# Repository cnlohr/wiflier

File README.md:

# wiflier, An ESP8266-based Quadcopter Brain

WARNING: This project is still in its early stages!  It doesn't fly yet!

WARNING: Everything surrounding a control loop in control.c for flight IS SUPER JANKEY AND TOTALLY NOT HOW IT SHOULD BE!

WARNING: When I operated the PWM at 3kHz, I had to modify my current board to add pullups on the I2C and short out the AVR's reset to VBat, otherwise it seemed to reboot randomly during flight.

Do you think quadcopters are neat?  Eh, not really for me... BUT I THINK ESP8266's ARE AWESOME!  So, I slapped an LSM9DS1 IMU, a BMP085 barometer and an AVR co-processor with 4 PWM output drivers to a PCB small enough to fit in a hubsan X4 quadcopter.

Picture of the wiflier brain

Youtube video of the first crack at this:

[!(http://img.youtube.com/vi/3n76iMTHXuE/0.jpg)](http://www.youtube.com/watch?v=3n76iMTHXuE) 

## The Hardware

There is an ESP8266, a 32-bit 80(or 160)MHz processor with 802.11bgn networking at the heart of the system.  This run all the user interface code, and handles all control algorithms.  It is attached to a 2 MByte flash for code and data storage.  It is connected via a software i2c bus to:

* An ATTiny441 with 4 PWM outputs and battery voltage monitoring.
   * 4 6-amp N-channel fets, with diode proection on the AVR's output channels to drive DC motors.
   * Safe-mode, which ramps PWM down after periods of inactivity.
* A LSM9DS1, 9-axis IMU with temperature sensor.  It has a gyro, accelerometer, and magnetometer built in.
* A BMP085, barometer with high precision temperature sensor built in.

## Network connectivity

The wiflier uses an ESP8266, which can act as either a station (mode 1) or a softap (mode 2).  Softap means it broadcasts a SSID that other compuers can connect to.

### Station (Mode 1)

Station mode can be initialized by the ```W1:[ssid]:password``` command.  This will cause the wiflier to connect to the specified network.  It supports WEP, WPA-PSK, and WPA2-PSK.  It will remember this setting when it boots up.  If it fails to connect, it will revert to mode 2.  Currently (maybe?) if it reverts to mode 2, it will stay in mode 2 every subsequent bootup.

If it succeeds in negotiating, it will pull a DHCP lease and print to the serial terminal what that DHCP release is.  All communicat

### Soft AP (Mode 2)

Soft AP mode allows the ESP8266 to create its own wifi network that you can connect to with a wifi-enabled device.  In this mode, one can connect to the new network, and visit the ESP at 192.168.4.1.

This is the default mode.

## Command Interfaces

There are currently two command interfaces to the wiflier.  One is UDP, on port 7777, the other is via HTTP at http://[ip]/d/issue?.

### The UDP interface

For the UDP interface, you can use netcat or 'nc' to communicate with the ESP.  This is partciularly convenient as a command-line tool. You can type

```
nc [ip] 7777 -u
```

To open a terminal to the wiflier.  You can type `T1` and enter.  This should provide a constant stream of telemetry.

When using the UDP interface, you must only have one command per packet.  Packets are the delineation of commands.

### The HTTP interface

If you make an HTTP request to `http://[ip]/d/issue?[command]` where [ip] is the address of the wiflier, and [command] is the command you are issuing, the command will be executed and its return value is sent.  You can check this interface's functionality by going to `http://192.168.4.1/d/issue?T0` and verify it returns a T0 confirmation.  Anything after the question mark will be urldecoded.  Things like amphersands should be URL encoded.

### The websockets interface.

This interface does not yet exist, but I hope to make it a reality.

## Building

This code is separated into two pieces, the ESP firmware and the AVR firmware.

The ESP firmware requires the esp_iot_sdk_v1.1.0, and a copy of the ESP8266 GCC toolchain.  To build the ESP firmware, cd to the espfirmware folder and type 'make'.

The AVR firmware requires avr-libc-1.8.0 and avr-gcc-4.8.1 at a minimum.  To build the AVR firmware, cd to the avr folder, and type 'make'.

## Memory layout:

We use a bit of a modified take on the old memory layout since, while we support OTA upgrades, we do so in a different way than the normal way.

| Address | Size  | Name / Description            |
| ------- |:-----:| ----------------------------- |
| 00000h  | 64k   | 0x00000.bin, IRAM Code        | 
| 10000h  | 180k  | Normally unused, HTTP may be here if signature found.  |
| 3C000h  | 4k    | May be used by web interface  |
| 3D000h  | 4k    | our device configuration      |
| 3E000h  | 8k    | May be used by ESP SDK.       |
| 40000h  | 240k  | 0x40000.bin, Cached code.     |
| 7C000h  | 8k    | May be used by ESP SDK.       |
| 7E000h  | 8k    | May be WiFi configuration     |
| 80000h  | 512k  | Scratchpad (Temp only!)       |
| 100000h | 1M+   | HTTP data, 1M on W25Q16.  HTTP Used here if signature found.       |

## Hardware designs

The wiflier schematics and PCB layout is done in KiCad (2013-07-03).  It should be compatible with newer versions, but is unlikely to be compatible with older versions.  In the hardware/ folder, you'll also find wiflier.lst.  This contains the part identifier, name, digikey part number (if applicable) and cost assuming an order of ~10 boards.

## wiflier UART

The UART on the wiflier is used to send debugging information.  The Wiflier does not currently accept commands via the UART.  I intend to make the UART available to GPS or video input.

## UART flashing the ESP8266.

To UART flash the ESP8266 you will need esptool.py and a serial TTL uart.  USB to serial converters are good. *Do not* use RS-232-level UARTs.  To flash this, you will need to:

1. De-power the device. 
2. Connect GPIO0 to GND.
3. Connect TX, RX and GND (And possibly power) to your UART, reversing TX/RX lines.
4. Apply power to the device.  
5. Then go to the espfirmware folder, and type:

    ```
    ~/esp8266/esptool/esptool.py --port /dev/ttyUSB0 write_flash 0x00000 0x00000.bin 0x40000 0x40000.bin
    ```
    
    or

    ```
    make burn
    ```

6. The esptool should reboot into the running code.

## Net flashing the ESP8266.

Net Flashing the ESP8266 is particularly easy.  Connect to the wiflier, verify you can communicate to it (via HTTP or ping).  Use the 'execute_reflash' tool with the following commands:

```
web/execute_reflash 192.168.4.1 0x00000.bin 0x40000.bin
```

or, from the espfirmware folder...

```
make netburn
```

This will connect to 192.168.4.1, and it will perform the following steps:

1. It will attempt to erase the blocks that need to be written (to 0x00000.bin) using the "FB" command.
  * And await confirmation.
2. It will write the data (0x00000.bin) using the "FW" command.
  * And await confirmation.
3. It will write this first file to 80000h, then it will repeat for the second file, to c0000h.
4. It will then compute the MD5 of the files and execute the "FM" command.
5. Internally, the wiflier will verify the integrety of the written files.
6. At this point, it will disable all interrupts.  Network will go down, etc.
7. It will copy the data from 80000h to 00000h, and then copy c0000h to 40000h.
8. It will then reboot itself and boot into the new code.
9. If a network wasn't found, and it switches to being its own AP... next boot, it should still try to join the old network.

## Flashing the AVR

The AVR is particularly easy to flash.  You'll need:

  * An ISP Programmer, like the TinyISP that operates a 3.3V outputs.
    * Under *NO* condition use a programmer that haves 5V outputs.  This will almost certainly cause severe damage to the wiflier.
  * Associated 6-pin ISP programming connector.
  * AVRDude, or other ISP programming software.
  * A 6-pin male-male connector, SMD preferred.

To flash, follow the following steps:

  1. Connect to a wiflier command interface.
  2. Use the "B0" command to make the ESP8266 release the bus.
    * Failure to do this may damage the AVR or ESP.
  3. Plug the 6-pin male connector into the programming header on the programmer.
  4. Hold the 6-pin connector on the back of the PCB. 
    * Reversing the order will not program, but will not damage the part.
    * You can determine proper order by unplugging power to the quadcopter and flipping the connector around until it powers on.  Powering on indicates proper order.
  5. Initiate programming of the AVR.
	* Failures may indicate the ESP is locking the bus lines.
    * Failures may indicate not all the pins are making contact.
    * Failures may indicate the programming header is reversed.
    * Failures may indicate other problems in the toolchain, i.e. not running programmer as root or having proper credentials.
  6. Remove programmer.
  7. Use the "B1" command to bring the ESP8266 Back online.

## TODO

### Software modifications:

* Try one-shotting the sensors (currently they're in free-run) this will synchronize them to the system clock.
* Try making the system switch over to calling the control loop on interrupt after connection is negotiated, rather than using flags and the idle loop.
* Add WebSockets?
* Add WebGL?
* Separate the control.c into different parts.
* Have some minimal levels of protection for writing to flash, i.e. maybe only allow writing to 0x80000+
* Send some sort of broadcast or discovery packets.
* Figure out why the AVR needs soooo many bytes before it accepts data.

### Hardware modifications:

* Consider making the sensors slaves to the AVR, and having the ESP communicate only to the AVR.
* Consider using the MPL3115A2 instead of the BMP085
* I keep looking at the lack of pullups on the I2C and it makes me nervous when we're running the motor controllers.

## Commands

The heart of the wiflier is the command engine.  This command engine is human-readable, and with the exception of some use cases of the flashing commands is human-readable.

Commands are very simple, they are basically single letters, then parameters, separated by colons.  Responses are usually similar to the command that was sent.  A failure can be indicated by either a lack of response, or an exclaimation point (!) prefixing the response.

As a warning, in some places \r\n is used and in others \n is used.  You should discard \r in all non-binary uses.

### Bn (B1 / B0):  Turn main control loop on/off
Turning the main control loop off will stop all I2C bus communication and resolving what to do in the control loop.  That also means telemetry will stop.

### D
Reboot the system.  This includes the bootloader.  If GPIO0 is held low, the serial bootloader will be initiated.

### Tn (T1 / T0):  Turn streaming of calibrated, filtered telemetry data on/off
This will either continously stream, or turn off streaming of the calibrated telemetry data from the sensors.  Calibration is done using the Rn and Z commands.  Data is tab deliniated.

The streaming format is: ```TD: [frame #]  [GyroX]  [GyroY]  [GyroZ]  [AccX]  [AccY]  [AccZ]  [MagX]  [MagY]  [MagZ]  [Pressure in Bar]  [Temperature in tenths of degrees C]  [battery voltage in 1/100ths of a volt]\n```

### Un (U1 / U0):  Turn streaming of uncalibrated/raw telemtry data on/off
This will enable/disable streaming of uncalibrated telemetry data, straight from the sensors.   Data is tab deliniated.

The streaming format is: ```UD: [frame #]  [GyroX]  [GyroY]  [GyroZ]  [AccX]  [AccY]  [AccZ]  [MagX]  [MagY]  [MagZ]  [Pressure in Bar]  [Temperature in tenths of degrees C]  [battery voltage in 1/100ths of a volt]\n```

For example:
```
UD   9224      600      199      137     2839     1790     2080       61     2214    -4673    101233    368    499 \r\n
UD   9225     -616     -244      304     3208     1797     1934       40     2229    -4673    101233    368    507 \r\n
UD   9226     -687     -234      318     3374     1815     1893       74     2259    -4683    101233    368    507 \r\n
UD   9227      242      240       43     2960     1795     2051       31     2223    -4691    101233    368    507 \r\n
UD   9228      455      146       46     3122     1708     1964       37     2226    -4664    101237    368    507 \r\n
```

### Z: Set 'zero'
Sending a Z will set the zero all gyros, and accelerometer X and accelerometer Y.  This will only have an effect on the calibrated, filtered telemetry data.

### Rn (R1 / R0): Enable range calibration.
When you want to begin range calibration (for accelerometer Z, and all mag inputs) send R1.  This will begin to look for peak positive and negative values.  When you execute R0, it will take whatever the maximums are and scale all data to that range.

### P: Print calibration and other system data.
When you send a 'P' command, the wiflier will send back all calibration and possibly other system data.  As of the time of writing this the following values are returned:

```
    P6
    #GC\t x \t y \t z (Gyro Zero)
    #AC\t x \t y \t z (Accelerometer Zero)
    #AL\t x \t y \t z (Accelerometer Minimum)
    #AM\t x \t y \t z (Accelerometer Maximum)
    #ML\t x \t y \t z (Magnetometer Minimum)
    #MH\t x \t y \t z (Magnetometer Maximum)
```

### S: Save calibration and other settings.
This writes the current information in the global `settings` value to the flash at address 3D000h.

### Mx: Motor control functions

#### M?: Motor query

Returns if motors are in automatic mode (1/0) and all motor speeds, 0..255 speed.

`M?` will return `M?[automatic]:[M0 speed]:[M1 speed]:[M2 speed]:[M3 speed]\r\n"

#### MA: Motors in automatic mode

Selecting this function will move the move the motors into automatic mode, allowing a control algorithm to take them over.

(Not currently implemented)

#### MM: Motors in manual mode

Disable automatic control of motors, they will now respond to the M(number) commands.  Optionally, can take up to 4 arguments for the new motor set values.

#### M0, M1, M2, M3: Set motor speed.

If you want to control an individual motor speed, you call `Mn:speed` for example `M0:127` would turn motor 0 on to half duty cycle.  This only works if the motors are in manual mode.

### Fx: Flash commands

#### FEn: Flash Erase Sector

Erase a specific flash sector, it will erase the flash starting at address n*4096 to n*4096+4095.  This function works with flash memory below and above the 1MB barrier, however it takes a moment to execute and no interrupts may run while it is executing.

#### FBn: Flash Erase Block

Erase a specific block of flash.  This operates on a whole 64kB block, and takes about as long as it takes FE to erase just one sector.  This function does not work past the 1MB barrier.

#### FW: Flash Write

This function writes flash. It requires two parameters, the first is the starting addres, the second is the size (in bytes).   Writes must be aligned to 4-byte boundaries, sizes must line to 4-byte boundaries.

```
    FW40:8:hello\r\n
```

Will write `hello\r\n\0` to memory address 40 (which will break booting, so don't do this), and it will respond with:

```
    FW40
```

#### FR: Flash Read

This will read back from the flash, starting at the first parameter and with length of the second.

```
    FR40:8\r\n
```

Will read from address 40 8 bytes and if we've executed the terrible terrible example above, respond with:

```
    FR00000040:0008:hello\r\n\0
```

#### FM: Rewrite boot flash

This function takes several parameters, in the style: ```FMa:b:c:d:e:f:g:h``` where 

   1. A = Address to copy from #1
   2. B = Address to copy to #1  (Must be 65kB aligned)
   3. C = Number of bytes to copy #1 (Must be 1k chunks)
   4. D = MD5 of entire 'from #1' range.
   5. E = Address to copy from #2
   6. F = Address to copy to #2  (Must be 65kB aligned)
   7. G = Number of bytes to copy #2 (Must be 1k chunks)
   8. H = MD5 of entire 'from #2' range.

This will verify both MD5's before copying.  Interrupts will continue to execute until the actual flash-over begins.  Once flash-over is complete, the device will automatically reboot.

An example would be:

```
FM524288:0:33792:d6f04e459bc9aefabd9ed80981e6837f:786432:262144:171008:8435d1904110eacb66771320f63736bc
```

It should respond with ```FM``` In the event of a failure, it will also send a ```!FM[code]```.

### Wx: Wireless/Network commands.

#### W1: Connect to wifi network.

If you want to connect to an existing wifi network, you can use the W1 command.  This will find the specified AP, and join.  An example W1 command would be ```W1:ssid:password```.  This will connect to network with name 'ssid', and password 'password'.  If it fails to connect, it will switch back to softap mode.

#### W2: Make softAP network

This will cause the ESP8266 to make its own network. You can connect to it.  Its IP will be 192.168.4.1

#### WI: Get current settings

This will cause the ESP8266 to give you the mode (1 or 2) SSID, and password of the current network status.

For example ```WI``` will return ```WI1:mynetwork:mypassword```.

#### WS: Scan for networks

**WARNING**: If operating in mode 2, this will cause the ESP to go offline momentarily while it scans!

If you issue the ```WS``` command, the ESP8266 will begin a scan. It is unlikely to return any response at all. You can read the returned networks with the ```WR``` command.

It may take several seconds for the WS command to complete.

#### WR: Return wireless networks from last scan.

After you scan for networks, you can probe for responses to those networks with the ```WR``` command.  It returns ```WRn``` where n is the number of networks found.  It will then provide the networks in a tab delinated data format as follows:

```
#SSID MAC RSSI Channel Encryption
```

For example a response to the ```WR``` command could be:

```
WR3
#quiddles       00:23:15:11:22:41       -44     1       open
#reads          08:18:a0:02:4d:cc       -55     1       wpa2
#rguest         0a:14:c1:f3:02:a0       -68     11      open
```

### J: Joystick commands

***SECTION NOT WRITTEN***

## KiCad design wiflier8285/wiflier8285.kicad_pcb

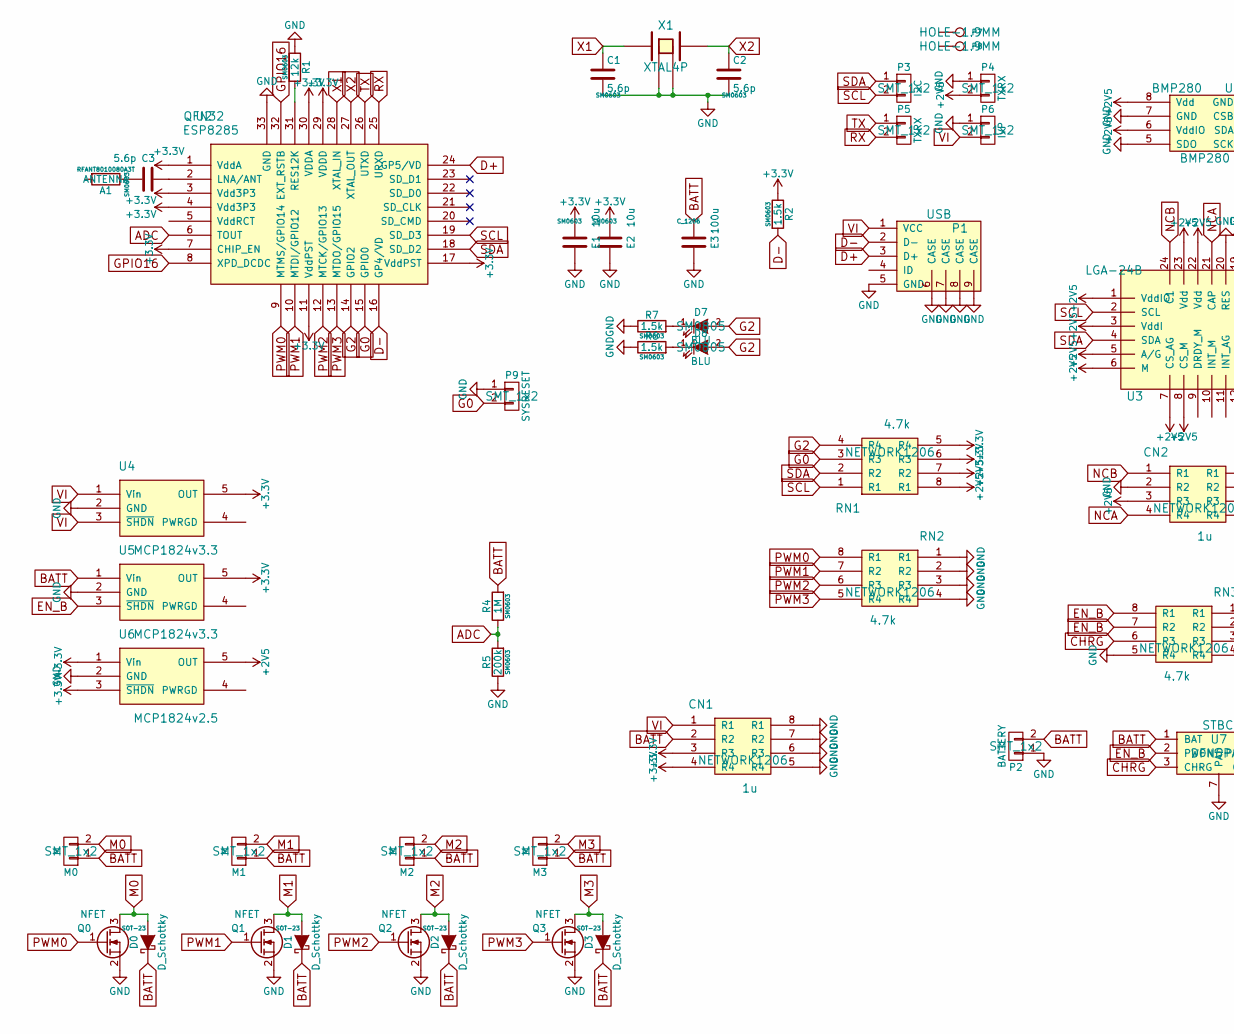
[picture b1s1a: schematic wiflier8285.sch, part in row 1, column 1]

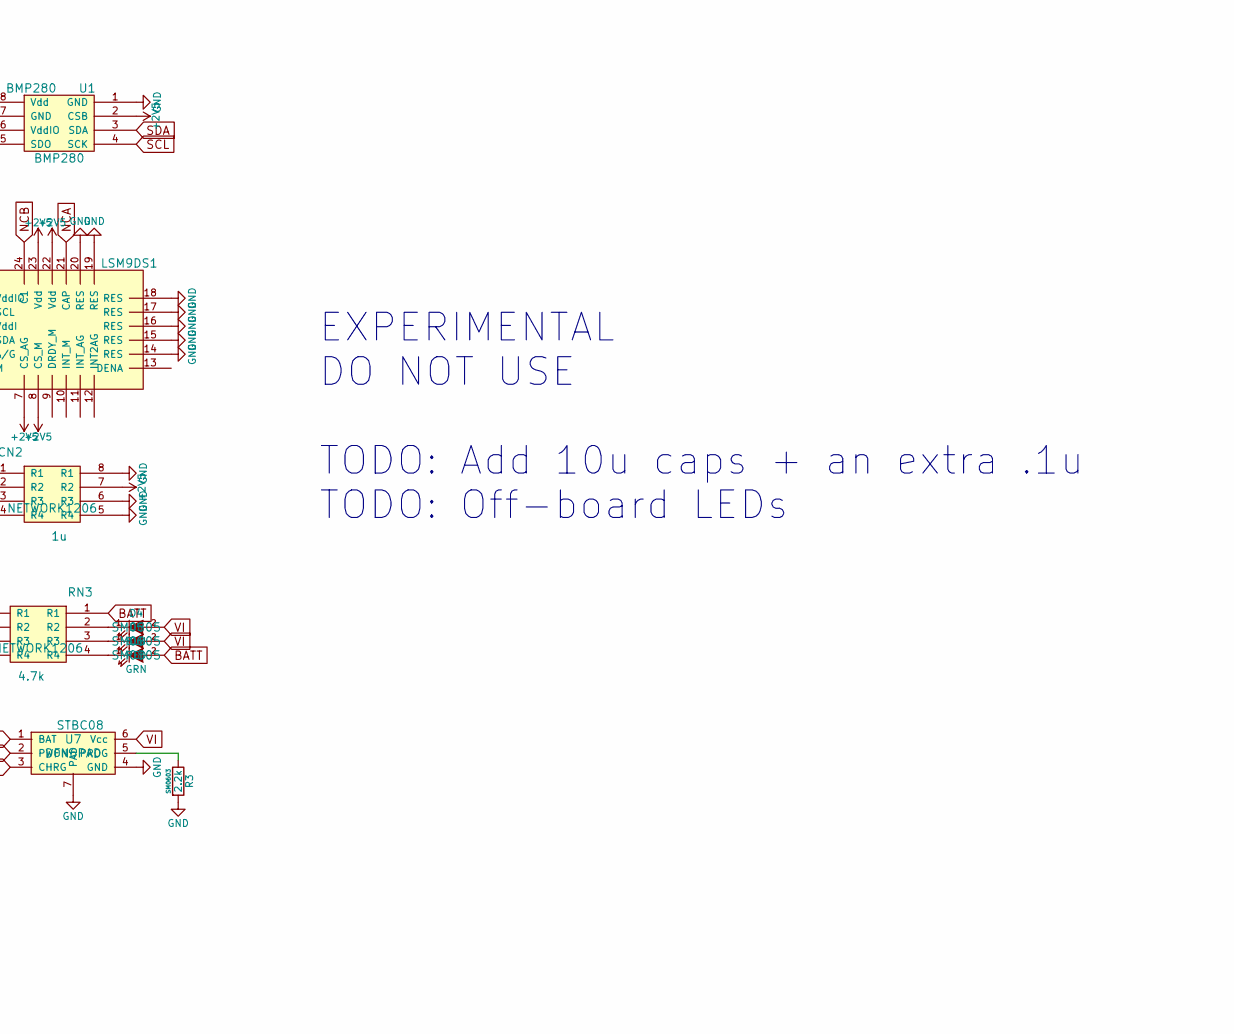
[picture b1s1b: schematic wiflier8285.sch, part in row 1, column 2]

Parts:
A1: ANTENNA; RFANT8010080A3T
C1, C2, C3: 5.6p; SM0603
CN1, CN2: 1u; NETWORK1206
D0, D1, D2, D3: D_Schottky; SMini2-F5-B; Digikey DB2J41100LCT-ND
D4, D7, D8: BLU; SM0805
D5: RED; SM0805
D6: GRN; SM0805
E1, E2: 10u; SM0603
E3: 100u; C_1206
M0, M1, M2, M3: M; SMT_1x2
P1: USB; USBMicroB-10118194-0001LF
P2: BATTERY; SMT_1x2
P3: I2C; SMT_1x2
P4, P5: TXRX; SMT_1x2
P6: IVP; SMT_1x2
P7, P8: M; HOLE-1.9MM
P9: SYSRESET; SMT_1x2
Q0, Q1, Q2, Q3: NFET; SOT-23; Digikey IRLML6244TRPBFCT-ND
R1: 12k; SM0603
R2, R6, R7: 1.5k; SM0603
R3: 2.2k; SM0603
R4: 1M; SM0603
R5: 200k; SM0603
RN1, RN2, RN3: 4.7k; NETWORK1206
U1: BMP280
U2: ESP8285; QFN32
U3: LSM9DS1; LGA-24B
U4, U5: MCP1824v3.3; SOT-23-5
U6: MCP1824v2.5; SOT-23-5
U7: STBC08; DFN6PAD
X1: XTAL4P; XTAL4TINY

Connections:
+2V5: CN2.3 (R3), CN2.7 (R2), P4.2, RN1.7 (R2), RN1.8 (R1), U1.2 (CSB), U1.6 (VddIO), U1.8 (Vdd), U3.1 (VddIO), U3.3 (VddI), U3.5 (A/G), U3.6 (M), U3.7 (CS_AG), U3.8 (CS_M), U3.22 (Vdd), U3.23 (Vdd), U6.5 (OUT)
+3V3: CN1.3 (R3), CN1.4 (R4), E1.2, E2.2, R2.1, RN1.5 (R4), RN1.6 (R3), U2.1 (VddA), U2.3 (Vdd3P3), U2.4 (Vdd3P3), U2.7 (CHIP_EN), U2.11 (VddPST), U2.17 (VddPST), U2.29 (VDDD), U2.30 (VDDA), U4.5 (OUT), U5.5 (OUT), U6.1 (Vin), U6.3 (~SHDN)
ADC: R4.1, R5.2, U2.6 (TOUT)
BATT: CN1.2 (R2), D0.1 (K), D1.1 (K), D2.1 (K), D3.1 (K), D6.2 (A), E3.2, M0.1, M1.1, M2.1, M3.1, P2.2, R4.2, RN3.1 (R1), U5.1 (Vin), U7.1 (BAT)
CHRG: RN3.6 (R3), U7.3 (CHRG)
D+: P1.3 (D+), U2.24 (GP5/VD)
D-: P1.2 (D-), R2.2, U2.16 (GP4/VD)
EN_B: RN3.7 (R2), RN3.8 (R1), U5.3 (~SHDN), U7.2 (PWON)
G0: P9.2, RN1.3 (R3), U2.15 (GPIO0)
G2: D7.2 (A), D8.2 (A), RN1.4 (R4), U2.14 (GPIO2)
GND: C1.2, C2.2, CN1.5 (R4), CN1.6 (R3), CN1.7 (R2), CN1.8 (R1), CN2.2 (R2), CN2.5 (R4), CN2.6 (R3), CN2.8 (R1), E1.1, E2.1, E3.1, P1.5 (GND), P1.6 (CASE), P1.7 (CASE), P1.8 (CASE), P1.9 (CASE), P2.1, P4.1, P6.1, P9.1, Q0.2 (S), Q1.2 (S), Q2.2 (S), Q3.2 (S), R1.1, R3.2, R5.1, R6.1, R7.1, RN2.1 (R1), RN2.2 (R2), RN2.3 (R3), RN2.4 (R4), RN3.5 (R4), U1.1 (GND), U1.5 (SDO), U1.7 (GND), U2.33 (GND), U3.14 (RES), U3.15 (RES), U3.16 (RES), U3.17 (RES), U3.18 (RES), U3.19 (RES), U3.20 (RES), U4.2 (GND), U5.2 (GND), U6.2 (GND), U7.4 (GND), U7.7 (PAD), X1.3 (GND), X1.4 (GND)
GPIO16: U2.8 (XPD_DCDC), U2.32 (EXT_RSTB)
M0: D0.2 (A), M0.2, Q0.3 (D)
M1: D1.2 (A), M1.2, Q1.3 (D)
M2: D2.2 (A), M2.2, Q2.3 (D)
M3: D3.2 (A), M3.2, Q3.3 (D)
NCA: CN2.4 (R4), U3.21 (CAP)
NCB: CN2.1 (R1), U3.24 (C1)
unnamed: A1.1, C3.2
unnamed: C3.1, U2.2 (LNA/ANT)
unnamed: D4.1 (K), RN3.2 (R2)
unnamed: D5.1 (K), RN3.3 (R3)
unnamed: D6.1 (K), RN3.4 (R4)
unnamed: D7.1 (K), R7.2
unnamed: D8.1 (K), R6.2
unnamed: R1.2, U2.31 (RES12K)
unnamed: R3.1, U7.5 (PROG)
PWM0: Q0.1 (G), RN2.8 (R1), U2.9 (MTMS/GPIO14)
PWM1: Q1.1 (G), RN2.7 (R2), U2.10 (MTDI/GPIO12)
PWM2: Q2.1 (G), RN2.6 (R3), U2.12 (MTCK/GPIO13)
PWM3: Q3.1 (G), RN2.5 (R4), U2.13 (MTDO/GPIO15)
RX: P5.2, U2.25 (URXD)
SCL: P3.2, RN1.1 (R1), U1.4 (SCK), U2.19 (SD_D3), U3.2 (SCL)
SDA: P3.1, RN1.2 (R2), U1.3 (SDA), U2.18 (SD_D2), U3.4 (SDA)
TX: P5.1, U2.26 (UTXD)
VI: CN1.1 (R1), D4.2 (A), D5.2 (A), P1.1 (VCC), P6.2, U4.1 (Vin), U4.3 (~SHDN), U7.6 (Vcc)
X1: C1.1, U2.28 (XTAL_IN), X1.1
X2: C2.1, U2.27 (XTAL_OUT), X1.2

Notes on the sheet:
EXPERIMENTAL DO NOT USE TODO: Add 10u caps + an extra .1u TODO: Off-board LEDs

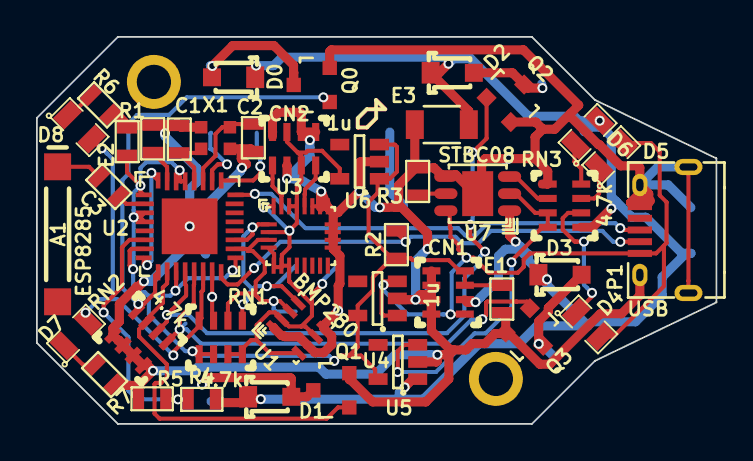
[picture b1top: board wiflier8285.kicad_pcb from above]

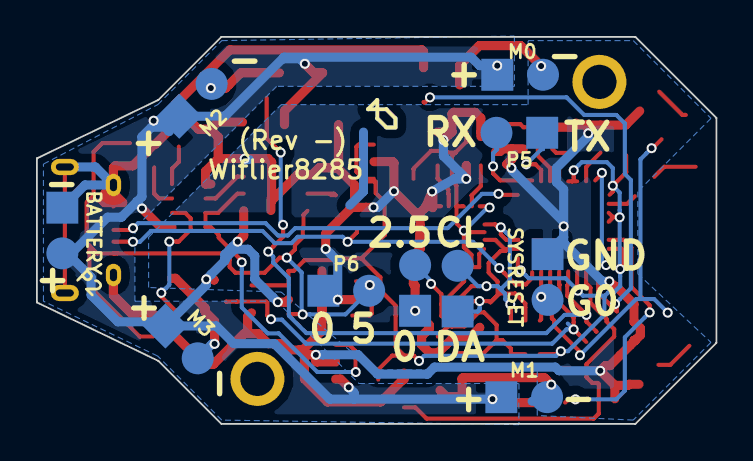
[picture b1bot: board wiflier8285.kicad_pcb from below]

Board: 2 copper layers, 37.8 x 21.5 mm, 53 parts (10 on the bottom side), 38 nets.

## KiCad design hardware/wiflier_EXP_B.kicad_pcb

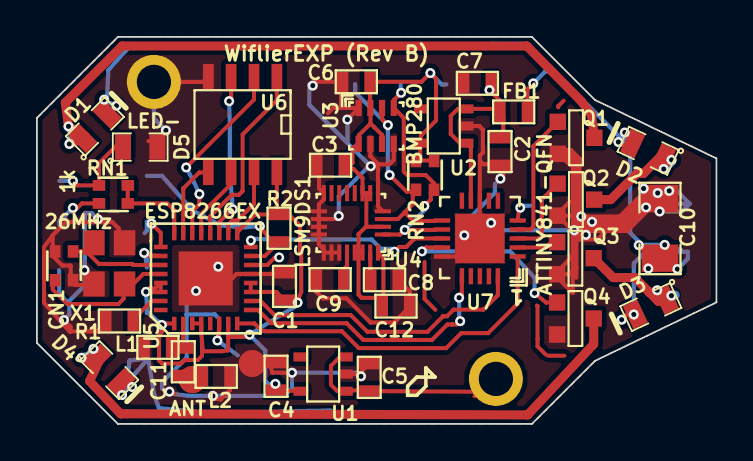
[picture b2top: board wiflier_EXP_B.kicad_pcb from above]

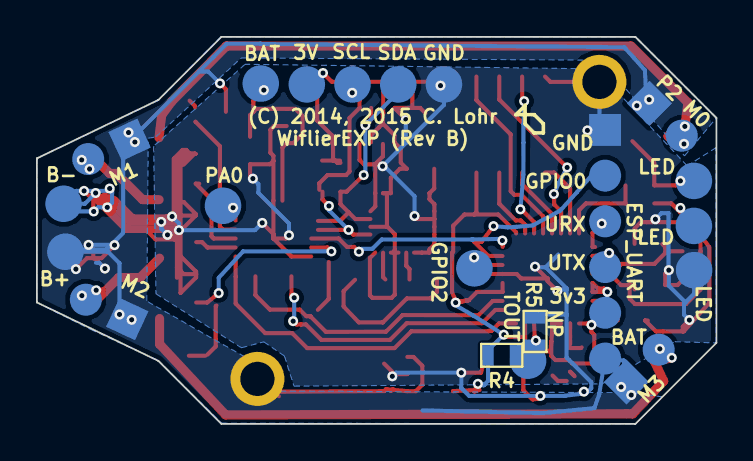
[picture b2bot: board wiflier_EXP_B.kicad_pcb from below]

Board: 2 copper layers, 37.8 x 21.5 mm, 61 parts (20 on the bottom side), 41 nets.

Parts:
C1, C2, C3, C5: 10uF; SM0603
C4: 1uF; SM0603
C6, C8, C12: .1u; SM0603
C7: .1uF; SM0603
C9: 10nF; SM0603
C10: 100uF; SM1206
C11: 5.6pF; SM0603
CN1: 10p; NETWORK0606
D1, D2, D3, D4: 20V_500mA; SM0805
D5: LED-; SM0805
FB1: -; SM0603
L1, L2: NP; SM0603
P1: GPIO2; .1SMTPIN
P2: M0; SMT_1x2
P3: M1; SMT_1x2
P4: M2; SMT_1x2
P5: M3; SMT_1x2
P6, P19: ANT; .1SMTPIN
P7, P8: HOLE-1.9MM
P9: SDA; .1SMTPIN
P10: SCL; .1SMTPIN
P11: 3V; .1SMTPIN
P12: GND; .1SMTPIN
P13, P14, P15: LED; .1SMTPIN
P16: BAT; .1SMTPIN
P17: TOUT; .1SMTPIN
P18: PA0; .1SMTPIN
P21: B+; .1SMTPIN
P24: B-; .1SMTPIN
P32: ESP_UART; SMT_1x6
Q1, Q2, Q3, Q4: 7A_20V; SOT23GDS
R1, R2, R4: 12k; SM0603
R5: NP; SM0603
RN1, RN2: 1k; NETWORK0606
U1: MCP1824/3.3; SOT23-5
U2: MCP1824/3.0; SOT23-5
U3: BMP280
U4: LSM9DS1; LGA-24B
U5: ESP8266EX; QFN32
U6: W25Q16DV; SO8E
U7: ATTINY841-QFN; QFN20
X1: 26MHz; XTAL4P

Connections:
+3.3V: C1.1, C4.1, P32.5, R2.2, R4.1, U1.5, U5.1, U5.3, U5.4, U5.7, U5.11, U5.12, U5.17, U5.29, U5.30, U6.8
+3.3VP: C3.1, C6.1, C12.1, P11.1, RN2.2, RN2.4, U2.5, U3.2, U3.6, U3.8, U4.1, U4.3, U4.7, U4.8, U4.22, U4.23
+BATT: C5.1, C10.1, D1.2, D2.2, D3.2, D4.2, FB1.2, P2.1, P3.1, P4.1, P5.1, P8.1, P21.1, P32.6, U1.1, U1.3
AVRMISO: U5.10, U7.20
AVRMOSI: U5.9, U7.16
AVRRST: U5.16, U7.13
AVRSCK: U5.8, U7.1
GND: C1.2, C2.2, C3.2, C4.2, C5.2, C6.2, C7.2, C8.1, C9.1, C10.2, C12.2, CN1.2, CN1.3, D5.2, L1.2, L2.2, P7.1, P12.1, P15.1, P19.1, P24.1, P32.1, Q1.S, Q2.S, Q3.S, Q4.S, R1.1, R5.2, U1.2, U2.2, U3.1, U3.5, U3.7, U4.5, U4.6, U4.13, U4.14, U4.15, U4.16, U4.17, U4.18, U4.19, U4.20, U5.13, U5.33, U6.4, U7.8, U7.15, U7.21, X1.3, X1.4
GP5: RN1.1, RN1.3, U5.24
GPIO0: P32.2, R2.1, U5.15
GPIO2: P1.1, U5.14
M0P: D1.1, P2.2, Q1.D
M1P: D2.1, P3.2, Q2.D
M2P: D3.1, P4.2, Q3.D
M3P: D4.1, P5.2, Q4.D
MTR0: Q1.G, U7.4
MTR1: Q2.G, U7.3
MTR2: Q3.G, U7.2
MTR3: Q4.G, U7.14
unnamed: P18.1, U7.5
unnamed: P13.1, RN1.2
unnamed: C8.2, U4.24
unnamed: C9.2, U4.21
unnamed: C11.1, L1.1, U5.2
unnamed: C11.2, L2.1, P6.1
unnamed: D5.1, P14.1, RN1.4
unnamed: R1.2, U5.31
unnamed: U5.20, U6.1
unnamed: U5.21, U6.6
unnamed: U5.22, U6.2
unnamed: U5.23, U6.5
unnamed: CN1.1, U5.28, X1.2
unnamed: U5.19, U6.3
unnamed: U5.18, U6.7
unnamed: CN1.4, U5.27, X1.1
SCL: P10.1, RN2.3, U3.4, U4.2, U7.12
SDA: P9.1, RN2.1, U3.3, U4.4, U7.11
TOUT: P17.1, R4.2, R5.1, U5.6
URX: P32.3, U5.25
UTX: P32.4, U5.26
VAA: C2.1, C7.1, FB1.1, P16.1, U2.1, U2.3, U7.9

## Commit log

2015-06-09 Initial commit from private repository to github.
    As a warning, a lot of this is barely tested and there are some minor, untested hardware changes, too.
2015-06-09 update rather embarrasing compiler error
2015-06-09 update main readme
2015-06-09 fix up the commands some
2015-06-10 total rework over a lot of stuff, now we have sort of closed loop control.
2015-06-10 more changes to readme
2015-06-11 Fix I2c timing some, avoid float's.
2015-06-11 add D command
2015-06-12 update to rev A
2015-06-13 update with correct i2c timing, better interpretation, and closing in on a control loop
2015-06-13 Update with driver for hand-held controllers
2015-06-13 Almost... now I'm getting faults on the IMU, and no idea why.
2015-06-13 add warnings
2015-06-13 do some very minor cleanup
2015-06-15 switch switching frequency up a lot.
    Seems to solve most problems.
2015-06-16 update readme... also, why did the binaries change?
2015-06-17 fix scanplace so it doesn't accumulate entries.
2015-06-23 Add wifiler A and B.
2015-06-23 remove wiflier A, keep B
2015-08-13 Woah, too many commits to count. I guess I just havne't committed anything here in a looong time.
2015-08-13 add new wiflier stuff
2015-08-16 major update - now able to push images and compaible with 1.3.0
2015-08-28 General updates with MPFS thing
2016-09-10 Add an initial stab at this new wiflier.
2016-09-13 Update!
2016-09-13 Remove extras
2016-09-14 update wiflier
2016-09-14 tweaks to output stuff
2016-10-30 add 8285 version of wiflier.

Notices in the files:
hardware/wiflier_EXP_B.kicad_pcb:
Copyright 2015 < Charles Lohr
(C) 2014, 2015 C. Lohr
